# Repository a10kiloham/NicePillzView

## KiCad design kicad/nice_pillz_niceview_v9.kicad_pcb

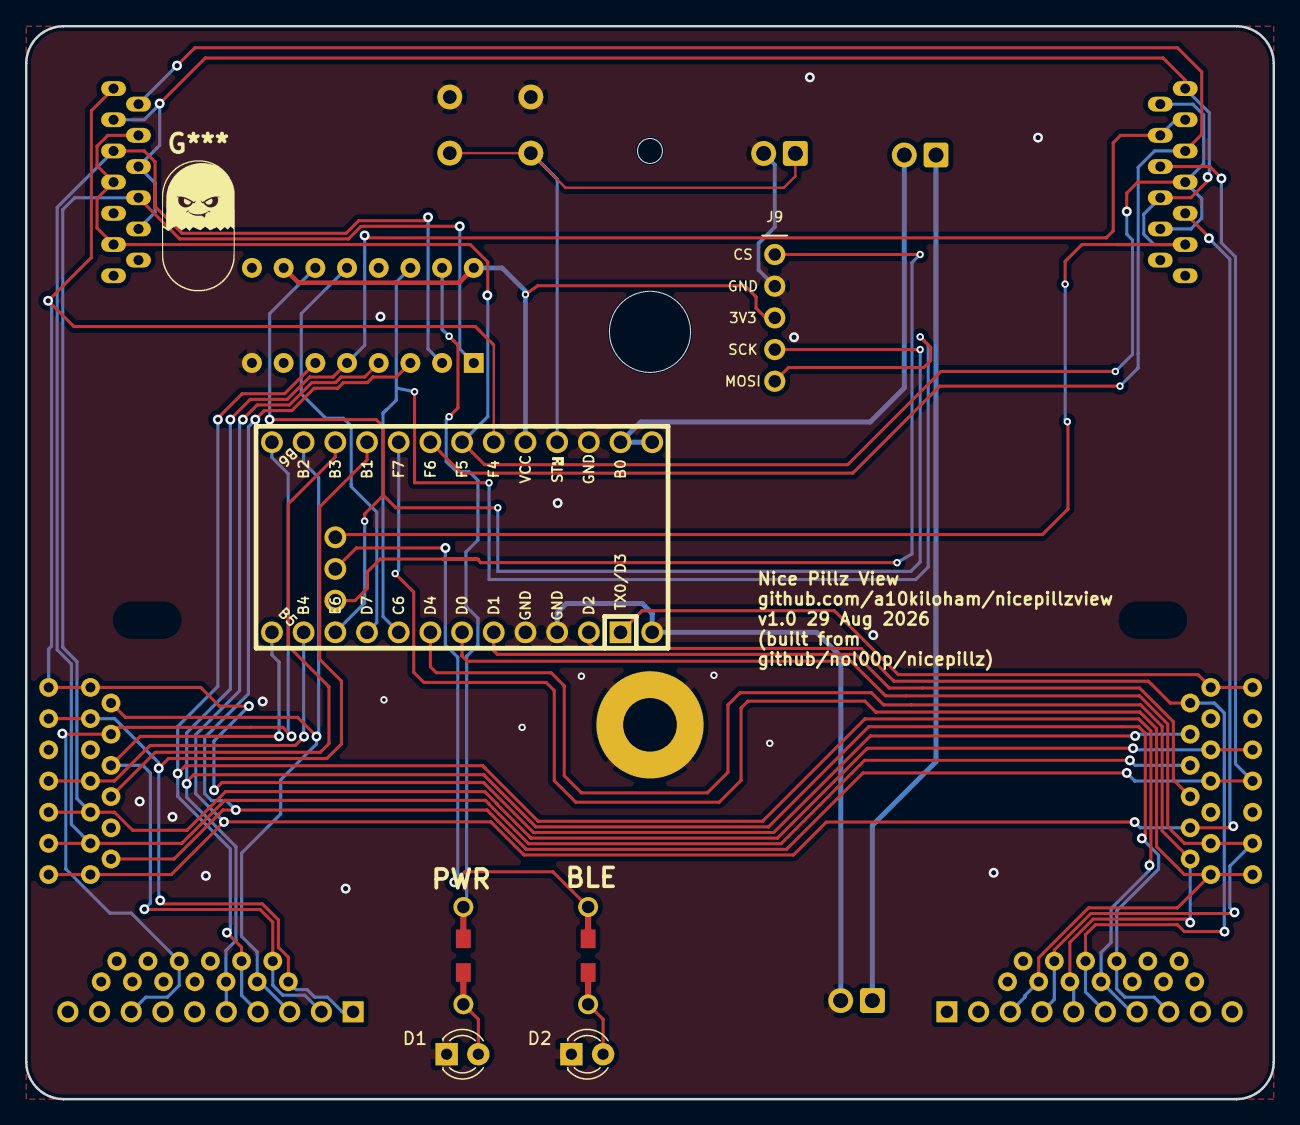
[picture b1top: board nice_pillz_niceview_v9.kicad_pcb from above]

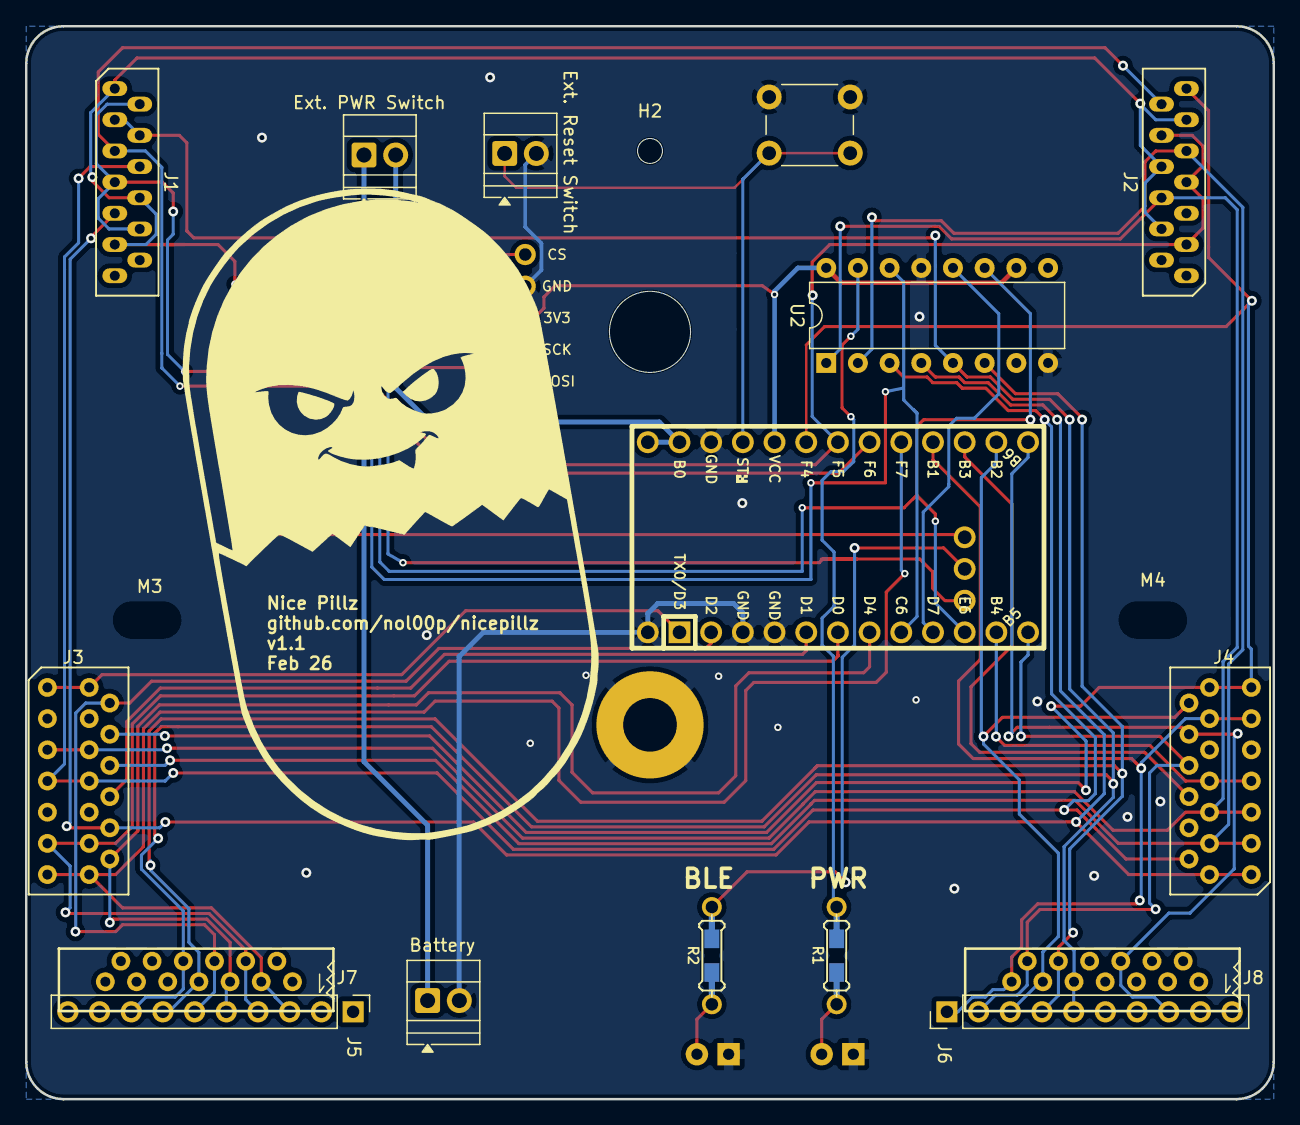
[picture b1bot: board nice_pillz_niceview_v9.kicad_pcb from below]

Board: 2 copper layers, 100.0 x 86.0 mm, 23 parts (19 on the bottom side), 35 nets.

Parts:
Battery: TerminalBlock_Xinya_XY308-2.54-2P_1x02_P2.54mm_Ho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; TerminalBlock_Xinya_XY308-2.54-2P_1x02_P2.54mm_Horizontal
D1: LED_CAPS; LED_D3.0mm
D2: LED_NUM; LED_D3.0mm
Ext. PWR Switch, Ext. Reset Switch: TerminalBlock_Xinya_XY308-2.54-2P_1x02_P2.54mm_Ho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; TerminalBlock_Xinya_XY308-2.54-2P_1x02_P2.54mm_Horizontal
H1: mounting pad; MountingHole_4.3mm_M4_Pad
H2: mounting pad; MountingHole_2mm
J1, J2: Conn_01x13; Molex_0039532135
J3, J4: Conn_01x13; Molex_039532134
J5, J6: Conn_01x10; Pin_Header_Straight_1x10_Pitch2.54mm
J7, J8: Conn_01x13; 39-53-2135
J9: NiceView; NiceView_1x05_P2.54mm_V
M1: MountingHole_6.4mm_M6
M3, M4: MountingHole_4.3mm_M4
R1, R2: R_US; Resistor-Hybrid
U1: nice!nanov2; nice_nano_v2
U2: 74HC595; DIP-16_W7.62mm

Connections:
+5V: J9.5, U1.21 (VCC), U2.10 (~SRCLR), U2.16 (VCC)
/COL_0: J2.13, J3.4, J4.13, U1.20 (A3/PF4)
/COL_1: J2.6, J3.5, J4.5, U2.1 (QB)
/COL_2: J2.9, J3.6, J4.3, U2.2 (QC)
/COL_3: J1.6, J3.7, J4.2, U2.3 (QD)
/COL_4: J1.9, J3.10, J4.1, U2.4 (QE)
/COL_5: J1.3, J1.4, J5.8, J6.5, J7.8, J8.9, U2.5 (QF)
/COL_6: J5.7, J6.4, J7.7, J8.10, U2.6 (QG)
/LATCH: U1.9 (6/PD7), U2.12 (RCLK)
/LED_CAPS_LOCK: J9.3, U1.26 (D5)
/LED_NUM_LOCK: R2.2, U1.27 (C7)
/PWR_LED: R1.2, U2.15 (QA)
/RESET: Ext. Reset Switch.1, U1.22 (RST)
/ROW_0: J4.6, U1.15 (14/PB3)
/ROW_1: J4.7, U1.11 (8/PB4)
/ROW_2: J4.8, J6.2, J8.12, U1.12 (9/PB5)
/ROW_3: J4.10, J6.8, J8.6, U1.13 (10/PB6)
/ROW_4: J4.11, J6.1, J8.13, U1.16 (15/PB1)
/ROW_5: J4.12, J6.3, J8.11, U1.14 (16/PB2)
/ROW_6: J3.13, J5.3, J7.3, U1.17 (A0/PF7)
/ROW_7: J3.11, J5.4, J7.4, U1.6 (3/PD0)
/ROW_8: J3.12, J5.5, J7.5, U1.7 (4/PD4)
/ROW_9: J3.2, J5.6, J7.6, U1.2 (RX1/PD2)
/ROW_10: J3.1, U1.1 (TX0/PD3)
/ROW_11: J3.8, U1.5 (2/PD1)
/ROW_12: J1.5, J2.12, U1.18 (A1/PF6)
/ROW_13: J1.1, J1.8, J1.11, J2.4, J2.8, J2.11, U1.28 (F1)
/ROW_14: J1.2, J1.7, J1.10, J2.3, J2.7, J2.10, U1.19 (A2/PF5)
/SPI_MOSI: J9.2, U1.8 (5/PC6), U2.14 (SER)
/SPI_SCK: J9.4, U1.10 (7/PE6), U2.11 (SRCLK)
BAT: Ext. PWR Switch.2, U1.24 (B0)
BAT+: Battery.1, Ext. PWR Switch.1
GND: Battery.2, D1.1 (K), D2.1 (K), Ext. Reset Switch.2, H1.1, J9.1, U1.3 (GND), U1.4 (GND), U1.23 (GND), U2.8 (GND), U2.13 (~OE)
unnamed: D1.2 (A), R1.1
unnamed: D2.2 (A), R2.1
